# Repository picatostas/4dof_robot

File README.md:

# 4dof_robot
This is the repository for my final degree project, including PCB files, Arduino Code, 3D files, etc.

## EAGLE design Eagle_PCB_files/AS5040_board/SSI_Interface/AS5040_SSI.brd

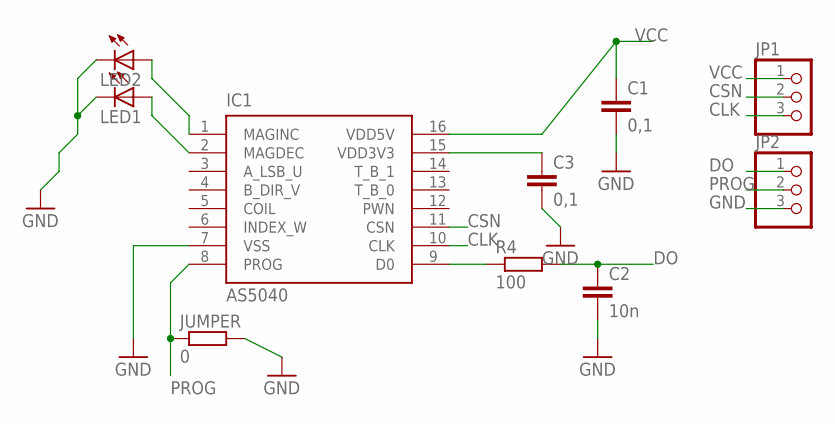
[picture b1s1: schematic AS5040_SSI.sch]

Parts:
C1, C3: 0,1; C0805
C2: 10n; C0805
IC1: AS5040; SSOP16
JP1, JP2: PINHD-1X3; 1X03
JUMPER: 0; M0805
LED1, LED2: LEDCHIPLED_0805; CHIPLED_0805
R4: 100; M0805

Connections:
CLK: IC1.10 (CLK), JP1.3
CSN: IC1.11 (CSN), JP1.2
DO: C2.1, JP2.1, R4.2
GND: C1.2, C2.2, C3.2, IC1.7 (VSS), JP2.3, JUMPER.2, LED1.C, LED2.C
unnamed: IC1.9 (D0), R4.1
unnamed: IC1.1 (MAGINC), LED2.A
unnamed: IC1.2 (MAGDEC), LED1.A
unnamed: C3.1, IC1.15 (VDD3V3)
PROG: IC1.8 (PROG), JP2.2, JUMPER.1
VCC: C1.1, IC1.16 (VDD5V), JP1.1

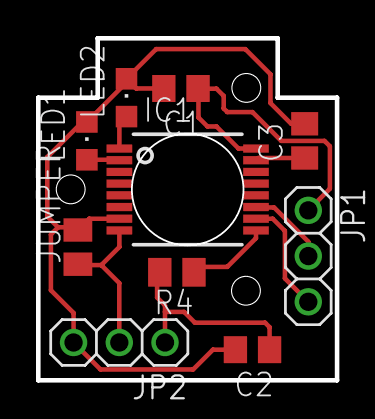
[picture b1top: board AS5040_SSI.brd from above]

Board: 2 copper layers, 16.6 x 19.0 mm, 10 parts (0 on the bottom side), 10 nets.

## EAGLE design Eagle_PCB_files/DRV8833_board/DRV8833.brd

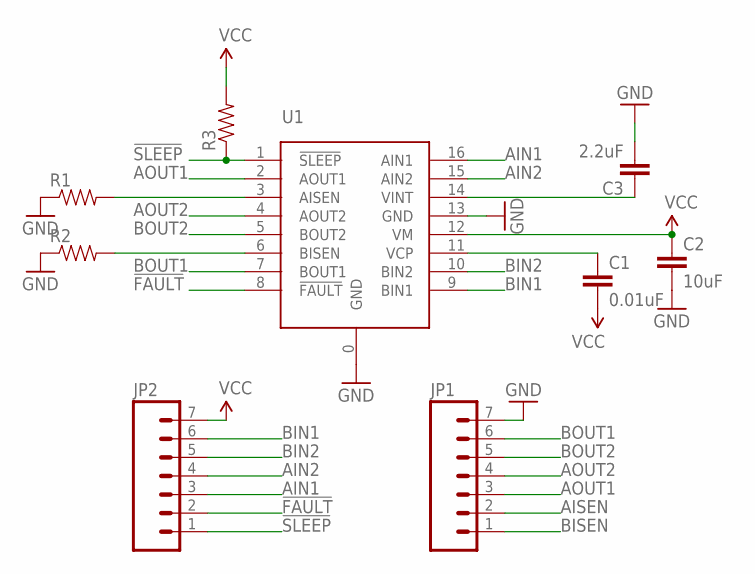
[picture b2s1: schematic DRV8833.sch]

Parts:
C1: 0.01uF; 0603-CAP
C2: 10uF; 1206
C3: 2.2uF; 0603-CAP
JP1, JP2: M07; 1X07
R1, R2: RESISTOR1206; 1206
R3: RESISTOR0603-RES; 0603-RES
U1: DRV8833; PWP16

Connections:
!FAULT: JP2.2, U1.8 (!FAULT)
!SLEEP: JP2.1, R3.1, U1.1 (!SLEEP)
AIN1: JP2.3, U1.16 (AIN1)
AIN2: JP2.4, U1.15 (AIN2)
AISEN: JP1.2, R1.2, U1.3 (AISEN)
AOUT1: JP1.3, U1.2 (AOUT1)
AOUT2: JP1.4, U1.4 (AOUT2)
BIN1: JP2.6, U1.9 (BIN1)
BIN2: JP2.5, U1.10 (BIN2)
BISEN: JP1.1, R2.2, U1.6 (BISEN)
BOUT1: JP1.6, U1.7 (BOUT1)
BOUT2: JP1.5, U1.5 (BOUT2)
GND: C2.2, C3.2, JP1.7, R1.1, R2.1, U1.0 (GND), U1.13 (GND)
unnamed: C1.1, U1.11 (VCP)
unnamed: C3.1, U1.14 (VINT)
VCC: C1.2, C2.1, JP2.7, R3.2, U1.12 (VM)

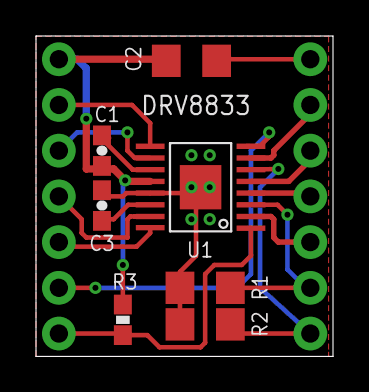
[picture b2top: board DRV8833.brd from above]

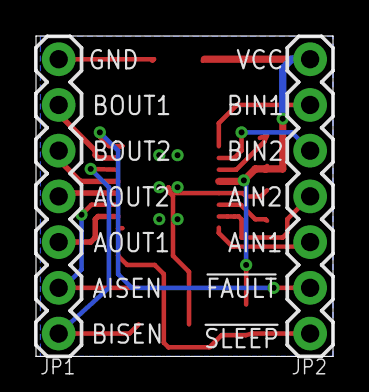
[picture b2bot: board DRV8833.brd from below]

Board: 2 copper layers, 16.5 x 17.8 mm, 9 parts (2 on the bottom side), 16 nets.

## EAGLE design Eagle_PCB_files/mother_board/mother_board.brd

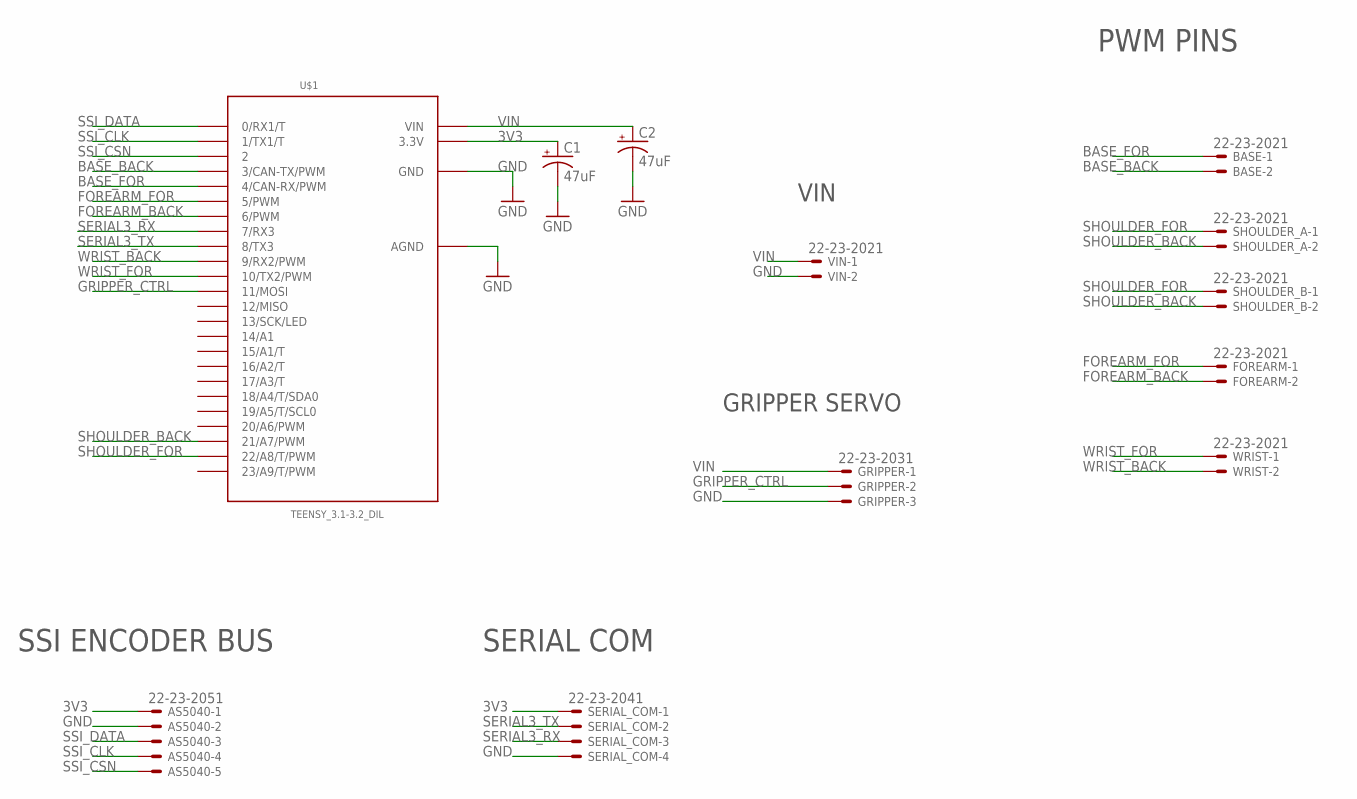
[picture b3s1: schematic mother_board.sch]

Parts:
AS5040: 22-23-2051
BASE: 22-23-2021
C1, C2: 47uF; E2,5-7
FOREARM: 22-23-2021
GRIPPER: 22-23-2031
SERIAL_COM: 22-23-2041
SHOULDER_A: 22-23-2021
SHOULDER_B: 22-23-2021
U$1: TEENSY_3.1-3.2_DIL; TEENSY_3.0-3.2&LC_DIL
VIN: 22-23-2021
WRIST: 22-23-2021

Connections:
3V3: AS5040.1, C1.+, SERIAL_COM.1, U$1.3.3V
BASE_BACK: BASE.2, U$1.3 (3/CAN-TX/PWM)
BASE_FOR: BASE.1, U$1.4 (4/CAN-RX/PWM)
FOREARM_BACK: FOREARM.2, U$1.6 (6/PWM)
FOREARM_FOR: FOREARM.1, U$1.5 (5/PWM)
GND: AS5040.2, C1.-, C2.-, GRIPPER.3, SERIAL_COM.4, U$1.AGND, U$1.GND, VIN.2
GRIPPER_CTRL: GRIPPER.2, U$1.11 (11/MOSI)
SERIAL3_RX: SERIAL_COM.3, U$1.7 (7/RX3)
SERIAL3_TX: SERIAL_COM.2, U$1.8 (8/TX3)
SHOULDER_BACK: SHOULDER_A.2, SHOULDER_B.2, U$1.21/A7 (21/A7/PWM)
SHOULDER_FOR: SHOULDER_A.1, SHOULDER_B.1, U$1.22/A8 (22/A8/T/PWM)
SSI_CLK: AS5040.4, U$1.1 (1/TX1/T)
SSI_CSN: AS5040.5, U$1.2
SSI_DATA: AS5040.3, U$1.0 (0/RX1/T)
VIN: C2.+, GRIPPER.1, U$1.VIN, VIN.1
WRIST_BACK: U$1.9 (9/RX2/PWM), WRIST.2
WRIST_FOR: U$1.10 (10/TX2/PWM), WRIST.1

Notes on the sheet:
PWM PINS
SSI ENCODER BUS
SERIAL COM
GRIPPER SERVO
VIN

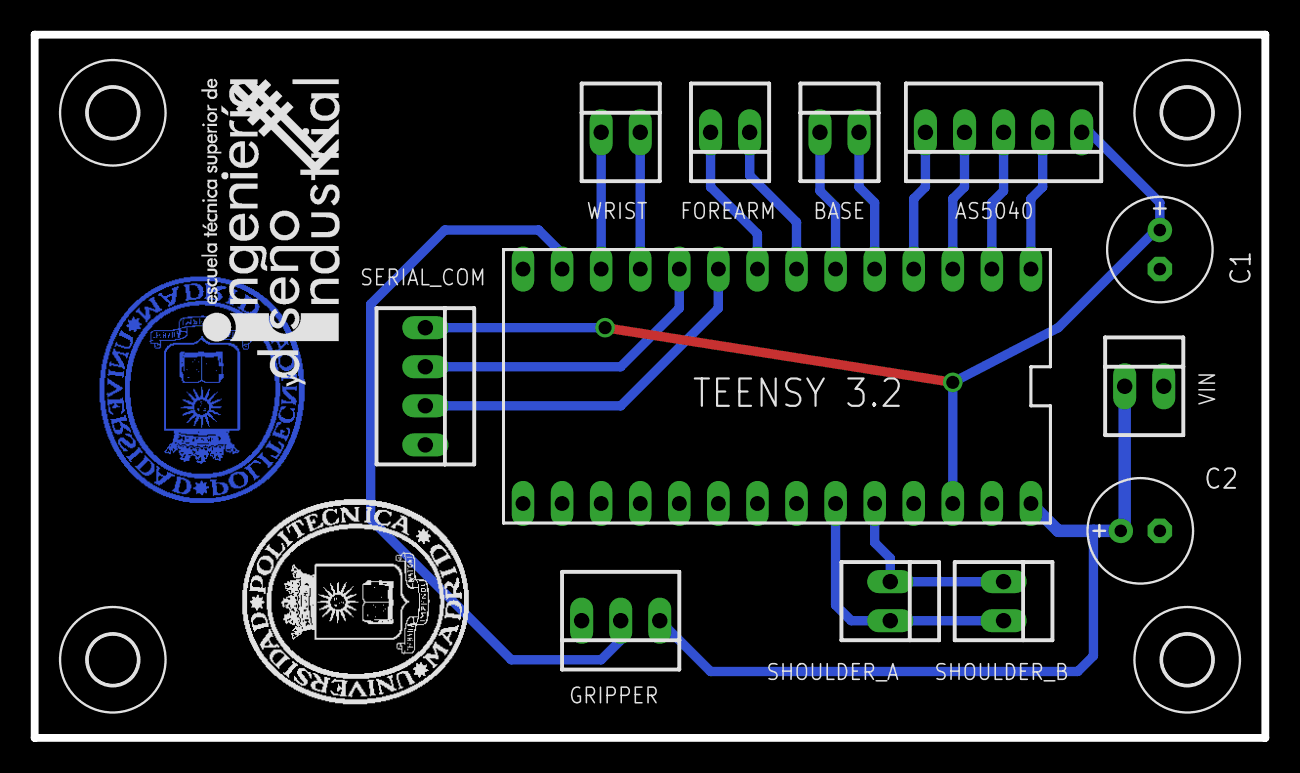
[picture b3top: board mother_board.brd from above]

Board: 2 copper layers, 80.0 x 45.7 mm, 19 parts (1 on the bottom side), 17 nets.

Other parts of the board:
U$2, U$3, U$4, U$5: 3,2
U$6: LOGO_UPM_NAMES
U$7: LOGO_ETSIDI_NAMES
U$8: LOGO_UPM_TOP1

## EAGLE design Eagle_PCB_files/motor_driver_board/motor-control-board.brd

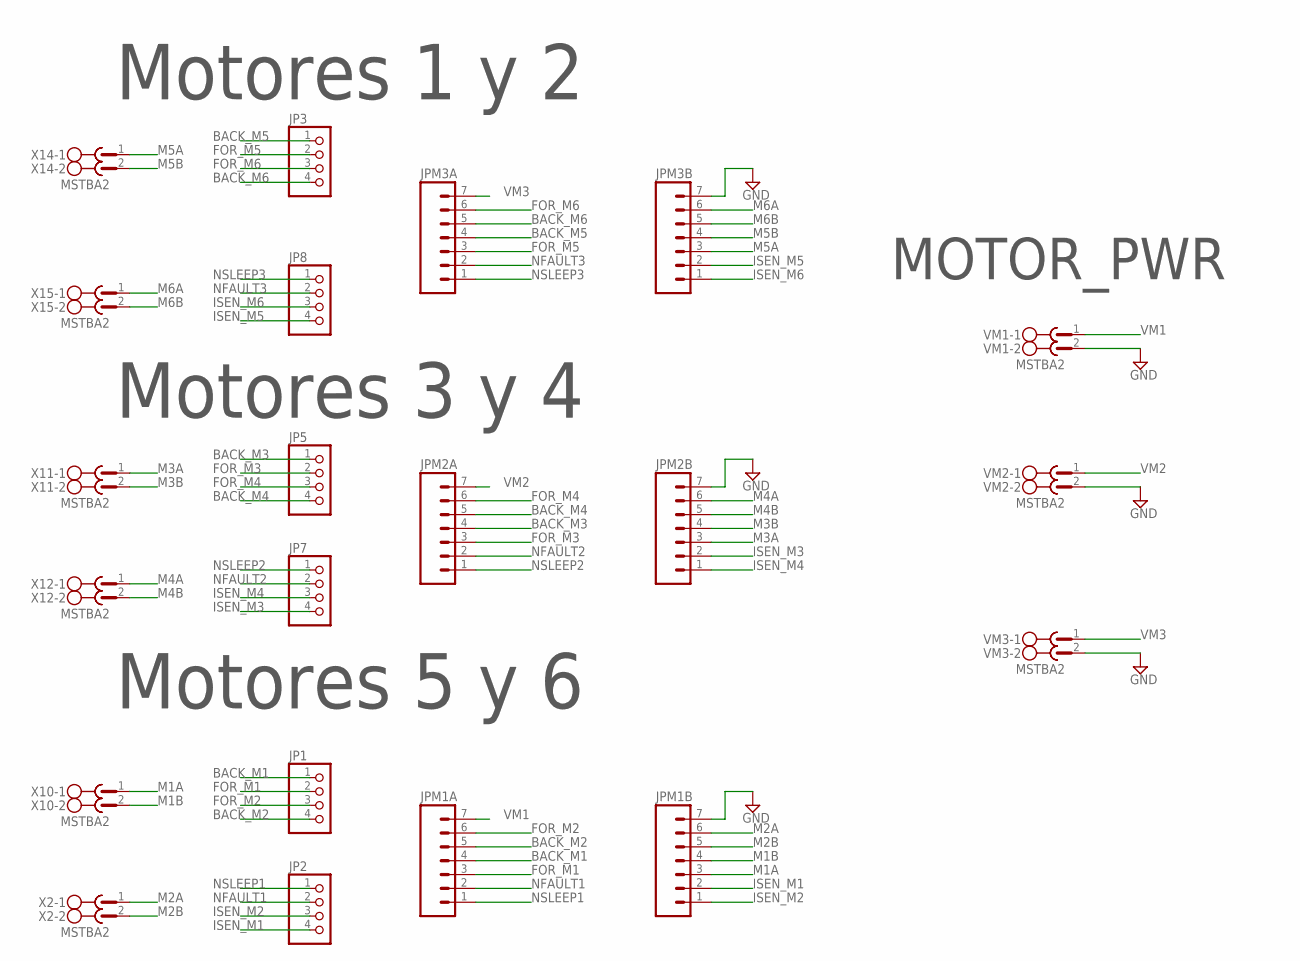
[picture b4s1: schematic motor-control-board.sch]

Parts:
JP1, JP2, JP3, JP5, JP7, JP8: PINHD-1X4; 1X04
JPM1A, JPM1B, JPM2A, JPM2B, JPM3A, JPM3B: M07; 1X07
VM1, VM2, VM3: MSTBA2
X2, X10, X11, X12, X14, X15: MSTBA2

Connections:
BACK_M1: JP1.1, JPM1A.4
BACK_M2: JP1.4, JPM1A.5
BACK_M3: JP5.1, JPM2A.4
BACK_M4: JP5.4, JPM2A.5
BACK_M5: JP3.1, JPM3A.4
BACK_M6: JP3.4, JPM3A.5
FOR_M1: JP1.2, JPM1A.3
FOR_M2: JP1.3, JPM1A.6
FOR_M3: JP5.2, JPM2A.3
FOR_M4: JP5.3, JPM2A.6
FOR_M5: JP3.2, JPM3A.3
FOR_M6: JP3.3, JPM3A.6
GND: JPM1B.7, JPM2B.7, JPM3B.7, VM1.2, VM2.2, VM3.2
ISEN_M1: JP2.4, JPM1B.2
ISEN_M2: JP2.3, JPM1B.1
ISEN_M3: JP7.4, JPM2B.2
ISEN_M4: JP7.3, JPM2B.1
ISEN_M5: JP8.4, JPM3B.2
ISEN_M6: JP8.3, JPM3B.1
M1A: JPM1B.3, X10.1
M1B: JPM1B.4, X10.2
M2A: JPM1B.6, X2.1
M2B: JPM1B.5, X2.2
M3A: JPM2B.3, X11.1
M3B: JPM2B.4, X11.2
M4A: JPM2B.6, X12.1
M4B: JPM2B.5, X12.2
M5A: JPM3B.3, X14.1
M5B: JPM3B.4, X14.2
M6A: JPM3B.6, X15.1
M6B: JPM3B.5, X15.2
NFAULT1: JP2.2, JPM1A.2
NFAULT2: JP7.2, JPM2A.2
NFAULT3: JP8.2, JPM3A.2
NSLEEP1: JP2.1, JPM1A.1
NSLEEP2: JP7.1, JPM2A.1
NSLEEP3: JP8.1, JPM3A.1
VM1: JPM1A.7, VM1.1
VM2: JPM2A.7, VM2.1
VM3: JPM3A.7, VM3.1

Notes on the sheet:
Motores 1 y 2
MOTOR_PWR
Motores 3 y 4
Motores 5 y 6

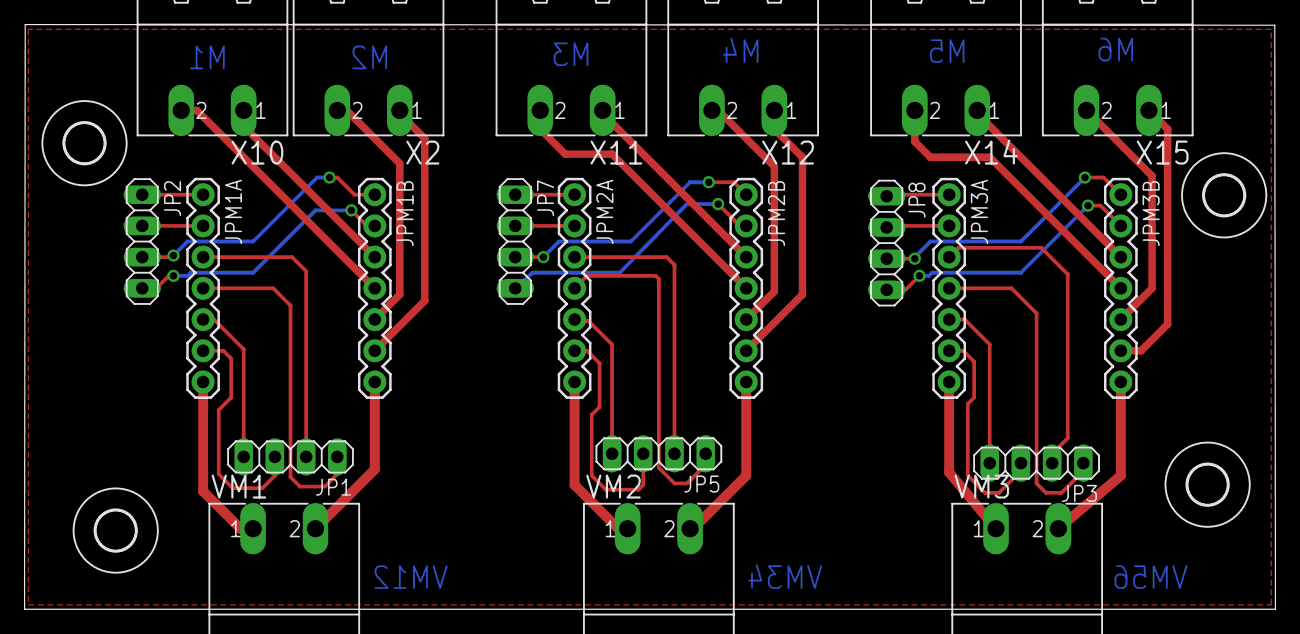
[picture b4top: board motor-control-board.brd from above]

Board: 2 copper layers, 101.8 x 47.6 mm, 25 parts (0 on the bottom side), 40 nets.

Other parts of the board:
U$10, U$11, U$12, U$13: 3,2

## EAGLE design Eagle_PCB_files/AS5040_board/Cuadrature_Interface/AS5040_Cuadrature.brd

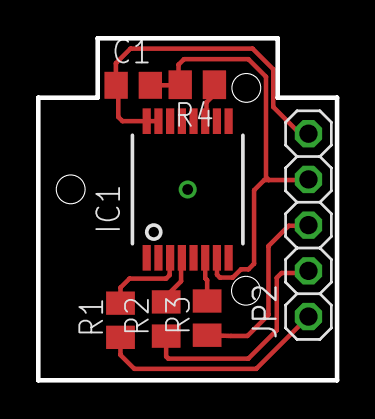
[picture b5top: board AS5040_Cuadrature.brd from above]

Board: 2 copper layers, 16.6 x 19.0 mm, 7 parts (0 on the bottom side), 9 nets.

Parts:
C1: 0,1; C0805
IC1: AS5040; SSOP16
JP2: 1X05
R1, R2, R3: 220; M0805
R4: 3k; M0805

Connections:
A: JP2.1, R1.1
B: JP2.2, R2.1
GND: C1.2, IC1.7, JP2.4, R4.2
IND: JP2.3, R3.1
unnamed: IC1.6, R3.2
unnamed: IC1.3, R1.2
unnamed: IC1.4, R2.2
unnamed: IC1.11, R4.1
VDD: C1.1, IC1.15, IC1.16, JP2.5

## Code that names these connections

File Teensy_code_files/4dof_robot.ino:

// INCLUDES
#include "AS5040.h"
#include "joint.h"
#include "Robot.h"
// DEFINES 
#define GDL 4

// PINES
#define SSI_DATA 0 // Rojo
#define SSI_CLK 1 // naranja
#define SSI_CSN 2 // amarillo 
#define M1A 4
#define M1B 3
#define M2A 22
#define M2B 21
#define M3A 5
#define M3B 6 
#define M4A 10 // 9 
#define M4B 9 // 10
#define GRIPPER_PIN 11
//
#define STEP   2500
#define PIDLIM 4095 // limitado por resolucion PWM
#define PWM_FREQ 549 // ideal para 16 bits, mantengo 12
#define PWM_RES 12 


#define L1 115
#define L2 75
#define L3 80
#define L4 89
#define intervals 4
#include <Metro.h> // Include the Metro library
#include <Servo.h>
Servo pinza;
Metro Sample_interval = Metro(5);  // Instantiate an instance
Metro Interpolation_time = Metro(150);
Metro read_time = Metro(5);
SSI _ssi{SSI_DATA,SSI_CLK,SSI_CSN};
double Serial_cords[GDL],Serial_pos[5];
bool cerrar_pinza = false,do_traj=false;
double q_traj[intervals][GDL];
bool traj_do = true;
int test_traj[10][5]={{180,250,120,173,0},
                      {180,225,130,120,0},
                      {180,200,145,120,1},
                      {180,200,130,150,1},
                      {180,240,118,120,1},
                      {245,240,118,120,1},
                      {245,200,132,124,0},
                      {245,245,105,124,0},
                      {180,308,94,106,0}};


int ramp =200 ;


int traj_count = 0;     //pinA,pinB,CWS,par_res,PWM_freq,limite_inf,limite_sup
int motor[GDL][7]= {    {M1A,M1B,0,600,PWM_FREQ,10,350},//2600 // pin A , pin B, CWS
                        {M2A,M2B,0,  0,PWM_FREQ,160,370},//2600
                        {M3A,M3B,0,  0,PWM_FREQ,60,300},//2700
                        {M4A,M4B,0,  0,PWM_FREQ,70,290}};//2500                                    

double kp=40.03, I= 96.43, D = 9.34;
double sample_time = 0.005,time_start = 0;

double time_serial,time_serial_prev,time_traj,time_traj_prev;


double elapsed_time,diff_time;
//double time_serial,time_serial_prev;
bool init = true;
double pos_ident,pos_ident_prev,volts_sp = 0;

Robot brazo_articulado(GDL,_ssi,motor,L1,L2,L3,L4); 

void setup(){
  
  Serial.begin(38400);
  
  delay(2000);
  brazo_articulado.readPos();
  brazo_articulado.init();
  pinza.attach(GRIPPER_PIN); // 120 CERRADO 150 ABIERTO
                              //kp,I,D,Ts,PID_lim, i-Joint
  brazo_articulado.setPID_param(50,0,3,sample_time,PIDLIM,0);
  brazo_articulado.setPID_param(50,0,5,sample_time,PIDLIM,1);
  brazo_articulado.setPID_param(60,0,4,sample_time,PIDLIM,2);
  brazo_articulado.setPID_param(40,0,4,sample_time,PIDLIM,3);
  time_start=millis();
  analogWriteResolution(PWM_RES);
  brazo_articulado.setSP(180,0);
  brazo_articulado.setSP(308,1);
  brazo_articulado.setSP(94 ,2);
  brazo_articulado.setSP(106,3);


  }

void loop(){

  float time_init = millis();
  /*
  while((time_init-time_start < 3000) && init){
    brazo_articulado.readPos();
    brazo_articulado.PID();
    delay(20);
  }
  if (time_init - time_start > 3000){
    init=false;
  }*/
  //time_traj=millis();

  //brazo_articulado.PID();
  brazo_articulado.readPos();

  if(cerrar_pinza){
    pinza.write(70);
  }
  else{
    pinza.write(100);
  }
  time_traj = millis();
  if (read_time.check() == 1){
    //brazo_articulado.printPos();
    time_serial_prev = millis();    
    Serial.print(time_serial_prev - time_serial);
    Serial.print("\t");
    Serial.print(cerrar_pinza);
    Serial.print("\t");
    brazo_articulado.PID();
  }
  
  if(Serial.available()){
    char cmd = Serial.read();
    switch (cmd){
      case '*':
        getSerialCoords();
        //delay(2000);
        break;
      case '#':
        getSerialPos();
       // delay(2000);
        break;
      case '$':
        getSerialPIDParam();
        //delay(2000);
        break;

    }
    time_serial = millis();
    time_serial_prev = 0;
    read_time.reset();
  }
/*
  if (traj_do && (time_traj - time_traj_prev >1500)){
    for (int i = 0; i < GDL; i++){
      brazo_articulado.setSP(test_traj[traj_count][i],i);
    }
    cerrar_pinza = test_traj[traj_count][4];
    traj_count++;
    if (traj_count >10) traj_do = false;
  }
  else{
    // aqui iria lo que va de normal 
  }*/
  time_serial_prev = time_serial; 
  time_traj_prev = time_traj;  
  
  
  
  
}
void getSerialCoords(){
  
      double qVector[GDL];      
      int pinza = Serial.parseInt();
      for(int i=0; i<GDL; i++){
        qVector[i] = Serial.parseInt();        
        if (qVector[i] > 1 ){
          brazo_articulado.setSP(qVector[i],i);
          Serial_cords[i]=(double)qVector[i];
        }
        if (pinza){
          cerrar_pinza = true;
        }
        else{
          cerrar_pinza = false;
        }
      }

      Serial.print("Serial coords : ");
      for (int i = 0; i < GDL; i++){
        Serial.print(qVector[i]);
        Serial.print("\t");
      }
      Serial.println();
      //traj();   
      //brazo_articulado.fkine(qVector);
}
       
void getSerialPos(){

  // x,y,z,phi,elbow_up,pinza unidades en mm
    double pVector[3];
    
    for(int i=0; i<3; i++){
      pVector[i]=Serial.parseInt();
      Serial_pos[i]=pVector[i];        
    }
    
    int phi = Serial.parseInt();

    int elbow_up = Serial.parseInt();
    int pinza = Serial.parseInt();
    if (pinza){
      cerrar_pinza = true;
    }
    else{
      cerrar_pinza = false;
    }
    Serial_pos[3]=phi;
    Serial_pos[4]=elbow_up;
    brazo_articulado.ikine(pVector,phi,elbow_up);
      
}
void traj(){
  double q_begin[GDL],q_end[GDL],q_diff[GDL];
  for (int i = 0; i < GDL; i++){
    q_begin[i]=brazo_articulado.getPosJoint(i);
    q_end[i]=Serial_cords[i];
    q_diff[i] = (q_end[i] -q_begin[i])/(intervals-1);
    Serial.print(q_begin[i]);
    Serial.print("\t");
    Serial.print(q_end[i]);
    Serial.print("\t");
    Serial.println(q_diff[i]);
  }

  for (int i = 0; i < intervals; i++){
    Serial.print("traj[] ");
    Serial.print(i);
    Serial.print(" : ");
    for (int j = 0; j < GDL;j++){
      q_traj[i][j]=q_begin[j]+q_diff[j]*i;
      Serial.print(q_traj[i][j]);
      Serial.print("\t");
    }
    Serial.println();
  }


}

void getSerialPIDParam(){

  // $nmumero_articulacion,kp,I,D,Ts
  int joint = Serial.parseInt();
  if(joint > 3 || joint < 0) return;
  float Kp =(float)(Serial.parseInt())/100.00;
  float I  =(float)(Serial.parseInt())/100.00;
  float D  =(float)(Serial.parseInt())/100.00;
  float Ts =(float)(Serial.parseInt())/100.00;
  Serial.print(joint);
  Serial.print("\t");
  Serial.print(Kp*100);
  Serial.print("\t");
  Serial.print(I*100);
  Serial.print("\t");
  Serial.print(D*100);
  Serial.print("\t");
  Serial.println(Ts*100);
  //delay(5000);
  brazo_articulado.setPID_param(kp,I,D,sample_time,PIDLIM,joint); 
  
}

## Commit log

2018-07-02 Initial commit for github
2019-06-12 Create LICENSE

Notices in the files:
parts and their libraries:
SparkFun-Aesthetics: Licensing: Creative Commons ShareAlike 4.0 International - https://creativecommons.org/licenses/by-sa/4.0
SparkFun-Passives: Licensing: CC v3.0 Share-Alike You are welcome to use this library for commercial purposes.
